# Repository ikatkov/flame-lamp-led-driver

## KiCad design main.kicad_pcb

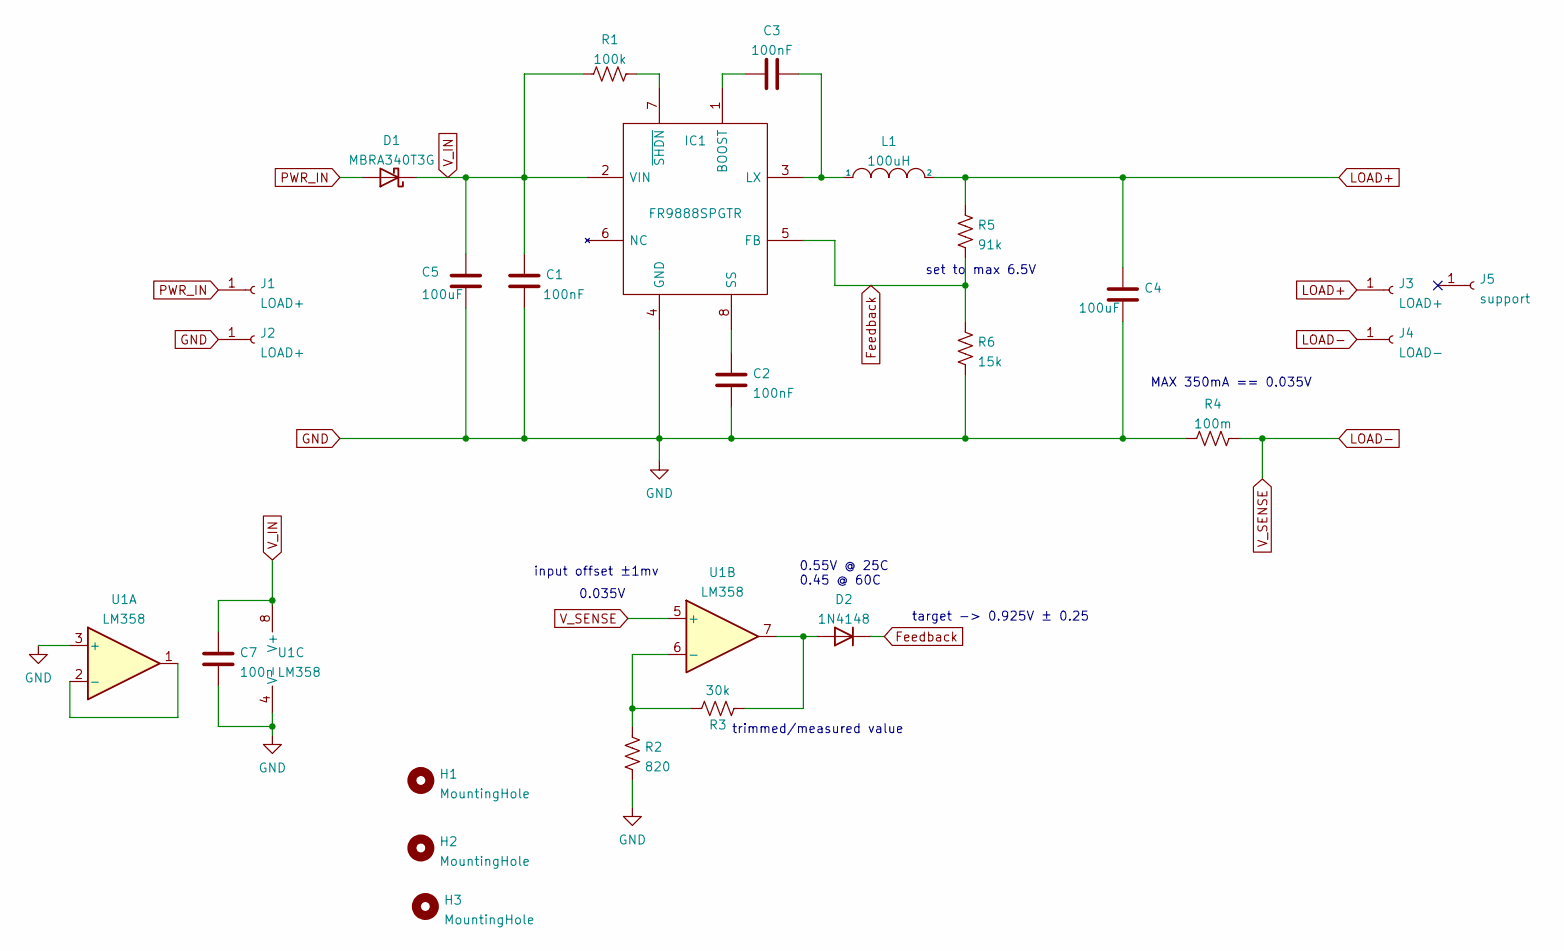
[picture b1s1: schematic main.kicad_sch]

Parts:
C1, C2, C3: 100nF; C_1206_3216Metric
C4: 100uF; CP_Radial_D5.0mm_P2.00mm
C5: 100uF; CP_Radial_D6.3mm_P2.50mm
C7: 100n; C_1206_3216Metric
D1: MBRA340T3G; D_SMA
D2: 1N4148; D_4148_SMD
H1, H2, H3: MountingHole; MountingHole_2.2mm_M2
IC1: FR9888SPGTR; SOIC-8-1EP_3.9x4.9mm_P1.27mm_EP2.514x3.2mm; Manufacturer_Part_Number FR9888SPGTR
J1, J2: LOAD+; SolderWire-0.5sqmm_1x01_D0.9mm_OD2.3mm
J3: LOAD+; SolderWire-slot
J4: LOAD-; SolderWire-slot
J5: support; SolderWire-slot
L1: 100uH; L_Taiyo-Yuden_NR-60xx_HandSoldering
R1: 100k; R_0805_2012Metric
R2: 820; R_0805_2012Metric
R3: 30k; R_0805_2012Metric
R4: 100m; R_2512_6332Metric
R5: 91k; R_0805_2012Metric
R6: 15k; R_0805_2012Metric
U1: LM358; SOIC-8_3.9x4.9mm_P1.27mm

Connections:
Feedback: D2.1 (K), IC1.5 (FB), R5.1, R6.2
GND: C1.2, C2.2, C4.2, C5.2, C7.2, IC1.4 (GND), J2.1, R2.2, R4.1, R6.1, U1.3 (+), U1.4 (V-)
LOAD+: C4.1, J3.1, L1.2, R5.2
LOAD-: J4.1, R4.2, U1.5 (+)
unnamed: C2.1, IC1.8 (SS)
unnamed: C3.1, IC1.3 (LX), L1.1
unnamed: C3.2, IC1.1 (BOOST)
unnamed: D2.2 (A), R3.2, U1.7
unnamed: IC1.7 (~SHDN), R1.2
unnamed: R2.1, R3.1, U1.6 (-)
unnamed: U1.1, U1.2 (-)
PWR_IN: D1.2 (A), J1.1
V_IN: C1.1, C5.1, C7.1, D1.1 (K), IC1.2 (VIN), R1.1, U1.8 (V+)

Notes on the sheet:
set to max 6.5V
0.035V
0.55V @ 25C 0.45 @ 60C
MAX 350mA == 0.035V
target -> 0.925V ± 0.25
trimmed/measured value
input offset ±1mv

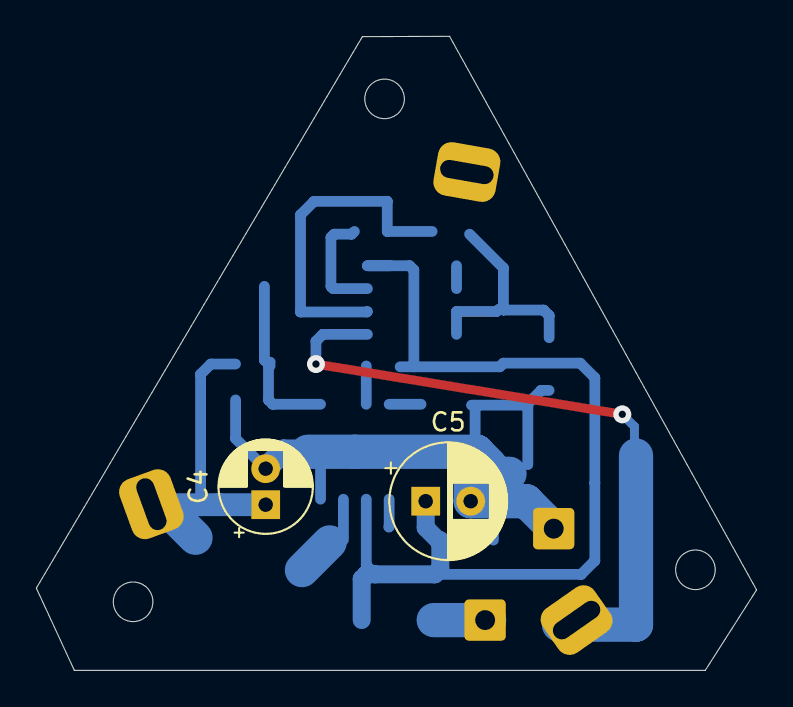
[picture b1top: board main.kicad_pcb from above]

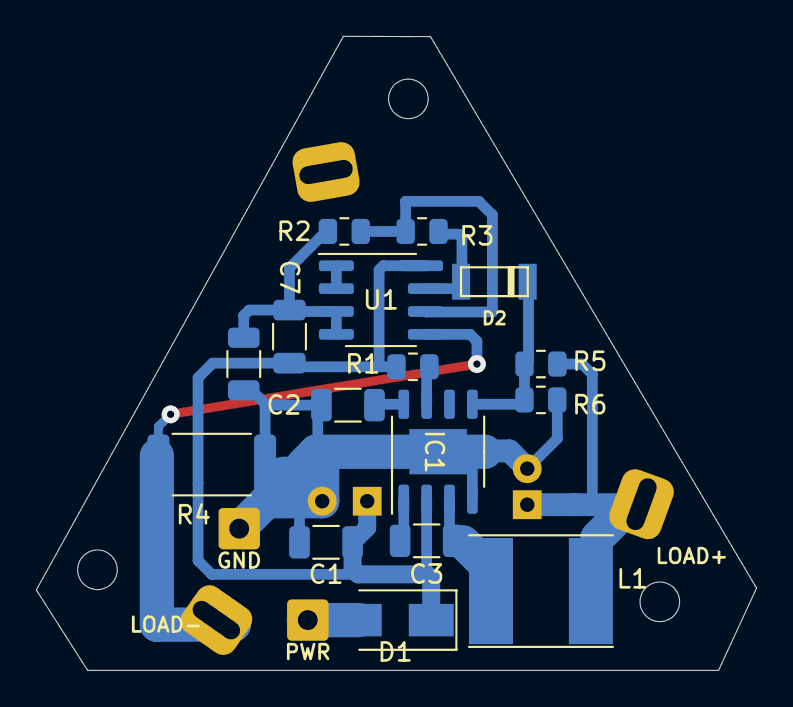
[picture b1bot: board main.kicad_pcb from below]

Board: 4 copper layers, 40.0 x 35.2 mm, 25 parts (21 on the bottom side), 13 nets.

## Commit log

2022-11-18 Initial
2022-11-19 last fixes
